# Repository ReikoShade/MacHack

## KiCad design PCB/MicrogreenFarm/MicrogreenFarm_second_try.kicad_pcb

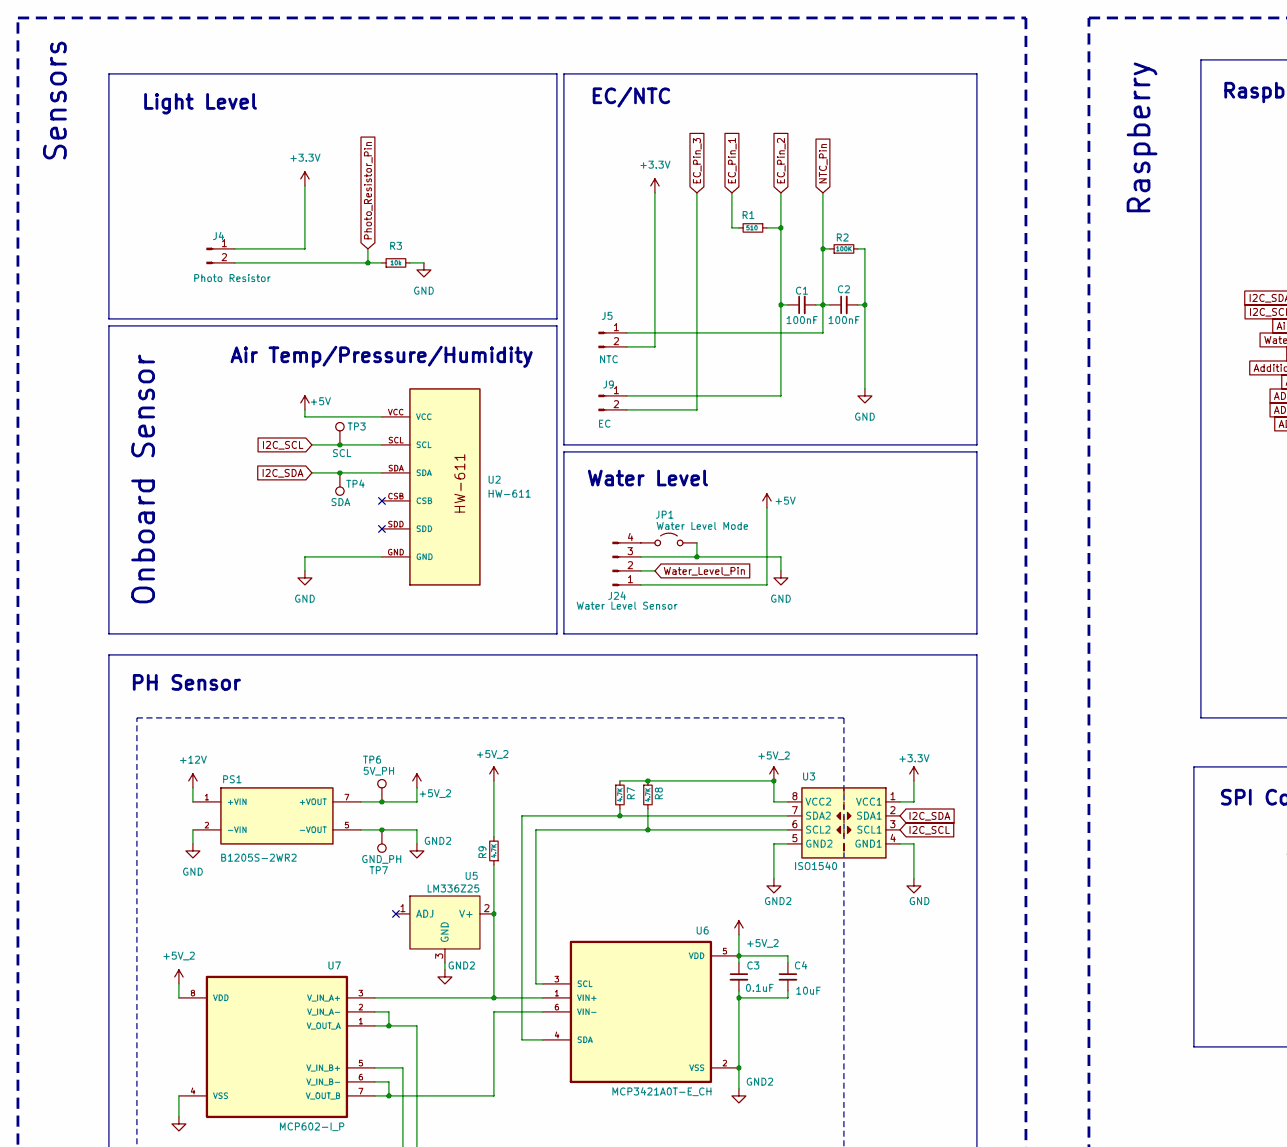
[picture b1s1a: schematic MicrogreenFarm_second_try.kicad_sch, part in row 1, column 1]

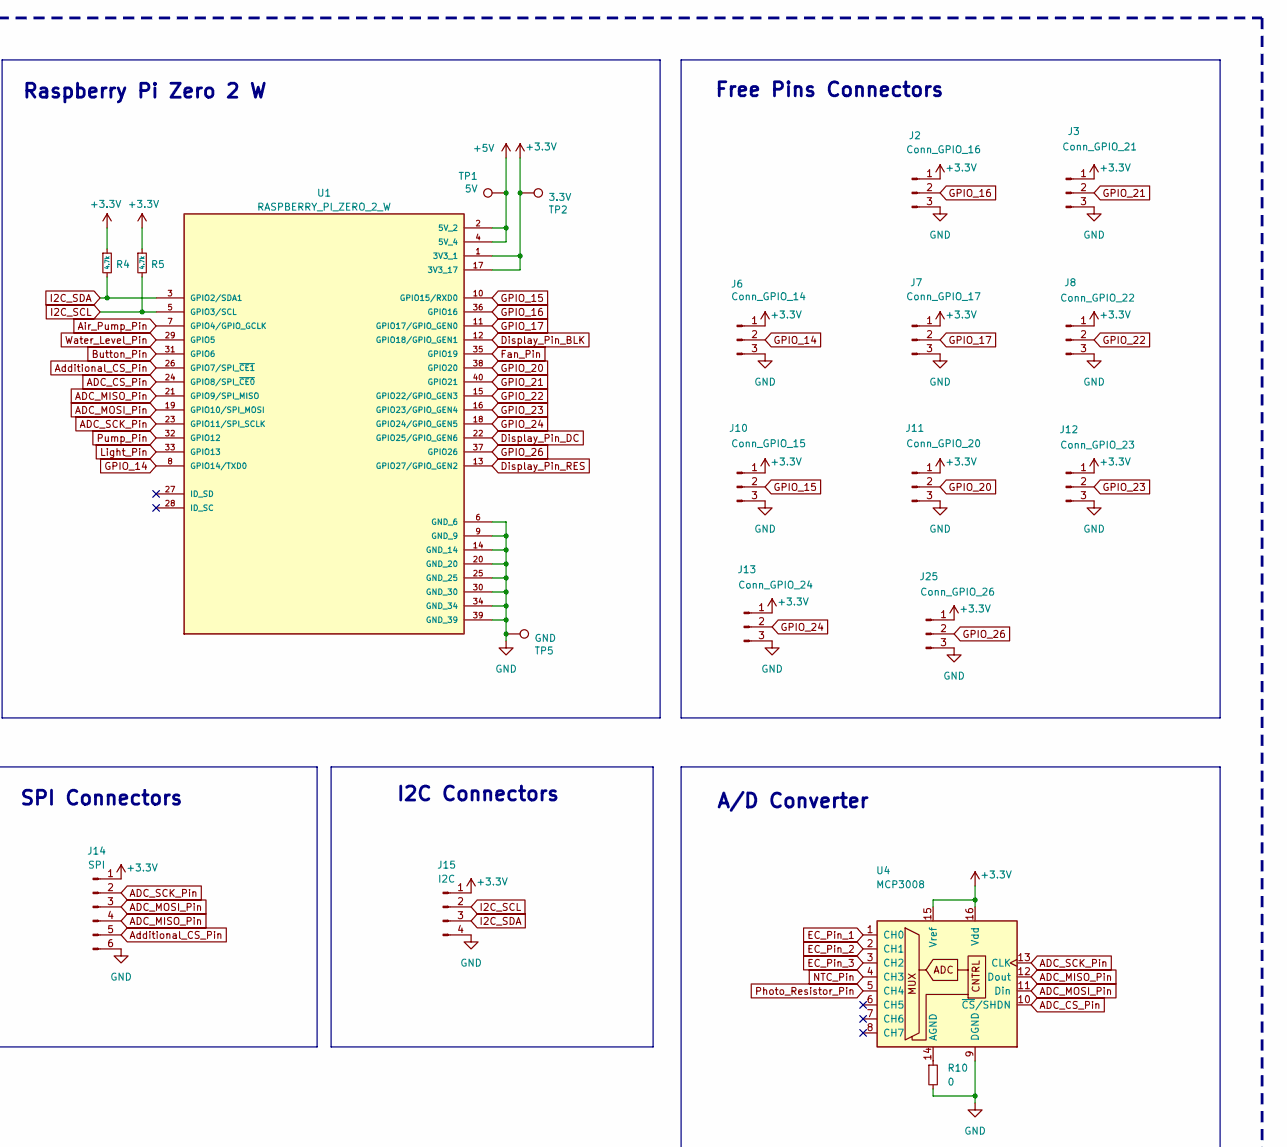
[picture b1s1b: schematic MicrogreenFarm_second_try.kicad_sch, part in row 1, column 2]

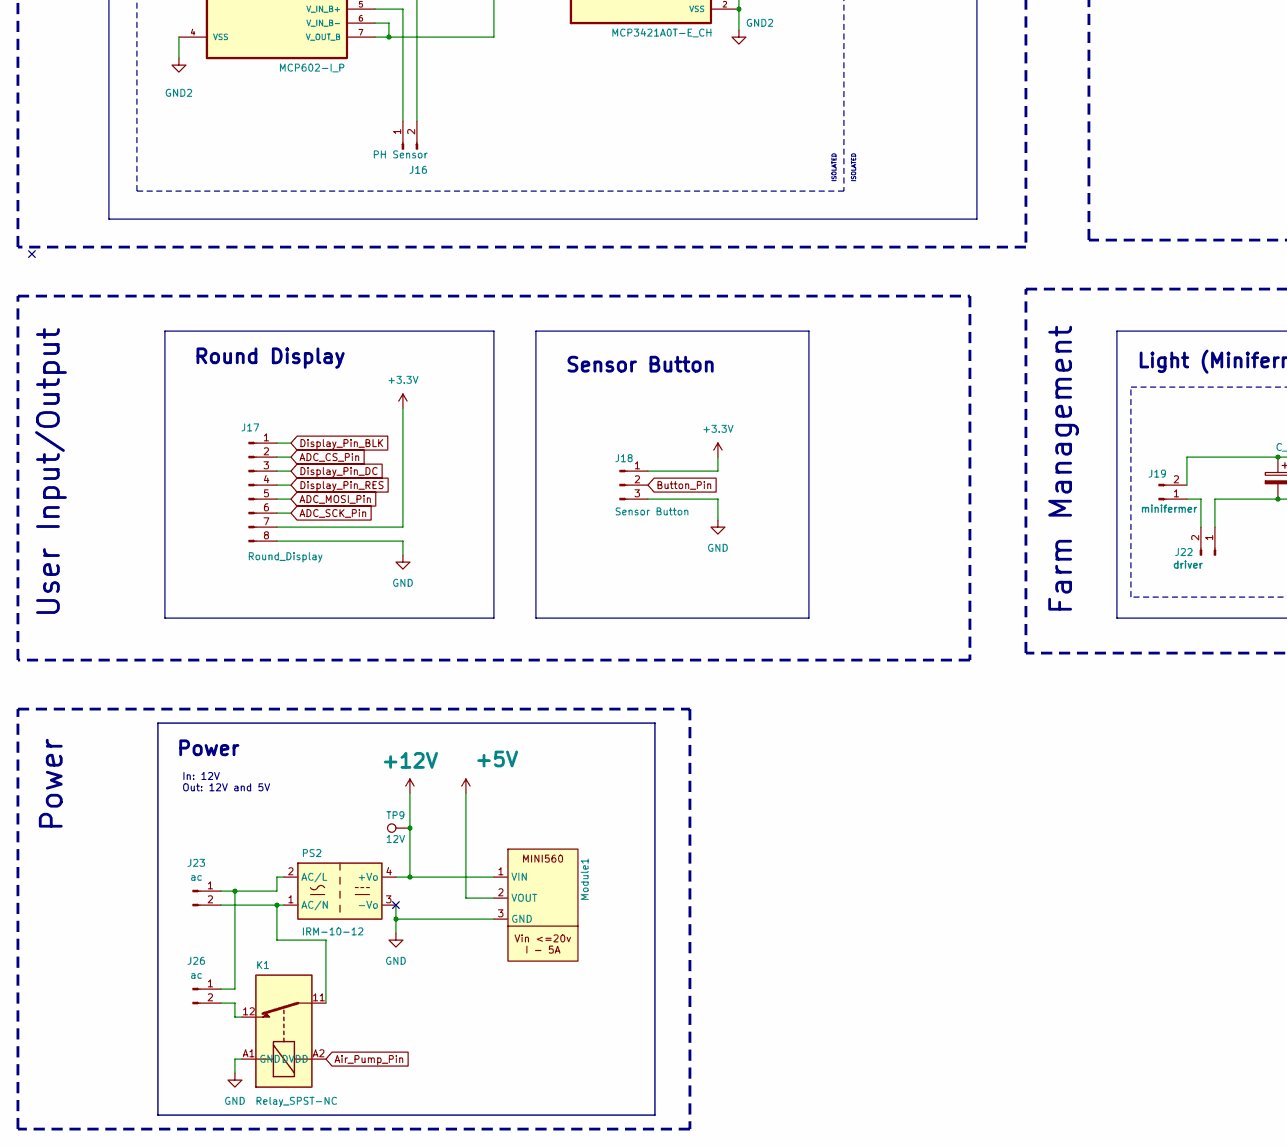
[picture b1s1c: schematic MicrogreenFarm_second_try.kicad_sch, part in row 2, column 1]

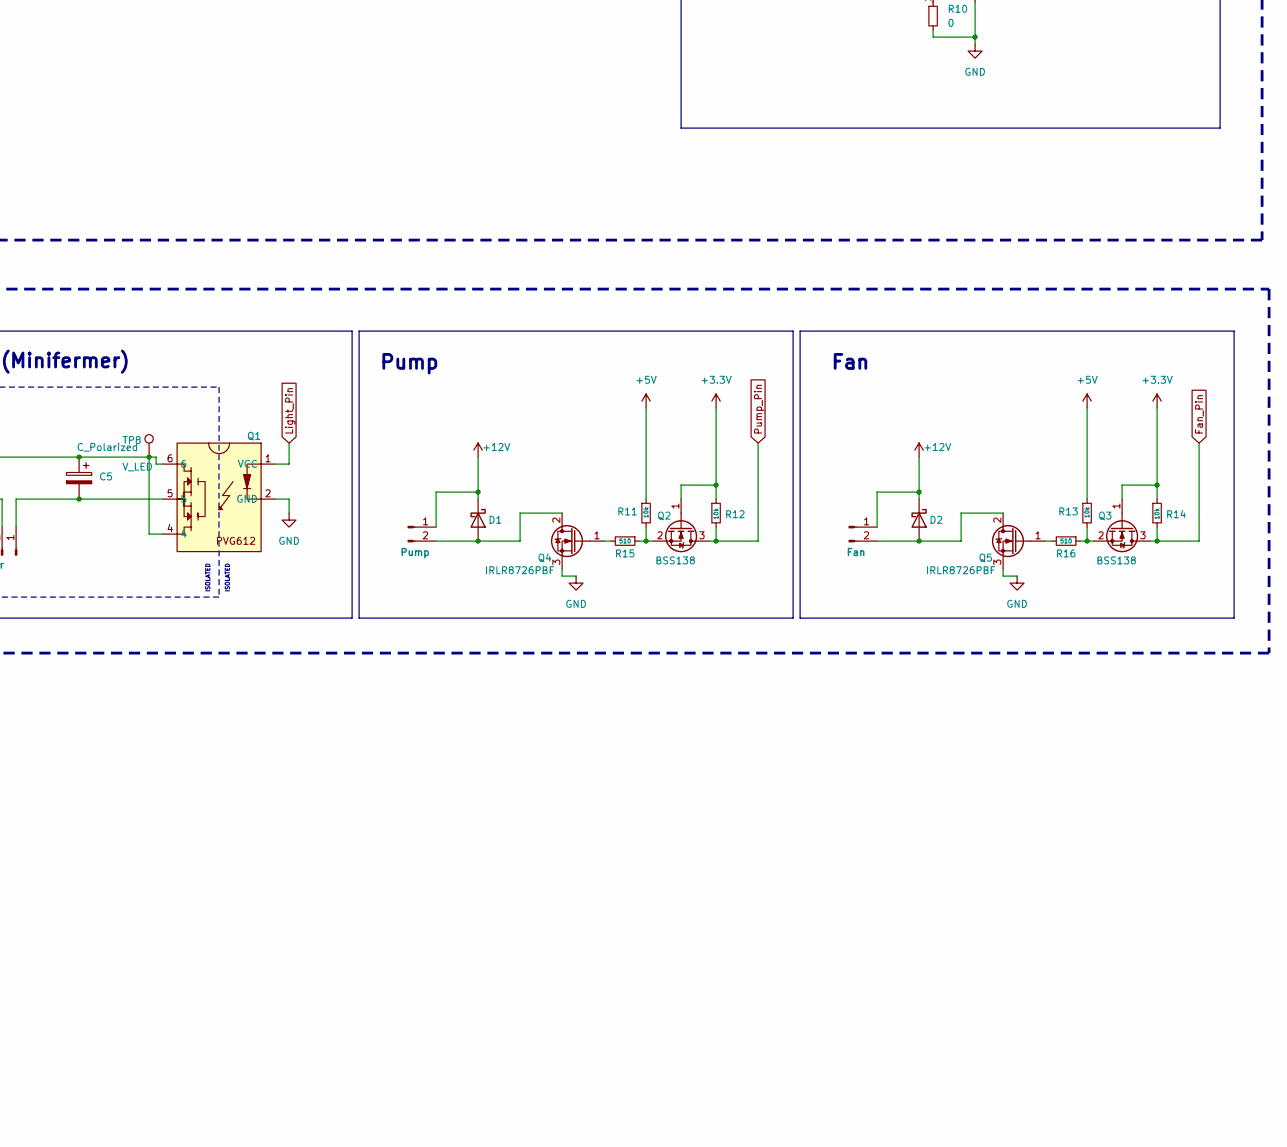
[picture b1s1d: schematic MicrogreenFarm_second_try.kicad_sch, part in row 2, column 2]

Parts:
C1, C2: 100nF; C_0402_1005Metric_Pad0.74x0.62mm_HandSolder
C3: 0.1uF; C_0402_1005Metric_Pad0.74x0.62mm_HandSolder
C4: 10uF; CP_EIA-3216-18_Kemet-A_Pad1.58x1.35mm_HandSolder
C5: C_Polarized; CP_Radial_D10.0mm_P3.80mm
D1, D2: SS34; D_SMA
J2: Conn_GPIO_16; PinHeader_1x03_P2.54mm_Vertical
J3: Conn_GPIO_21; PinHeader_1x03_P2.54mm_Vertical
J4: Photo Resistor; JST_XH_B2B-XH-A_1x02_P2.50mm_Vertical
J5: NTC; JST_XH_B2B-XH-A_1x02_P2.50mm_Vertical
J6: Conn_GPIO_14; PinHeader_1x03_P2.54mm_Vertical
J7: Conn_GPIO_17; PinHeader_1x03_P2.54mm_Vertical
J8: Conn_GPIO_22; PinHeader_1x03_P2.54mm_Vertical
J9: EC; JST_XH_B2B-XH-A_1x02_P2.50mm_Vertical
J10: Conn_GPIO_15; PinHeader_1x03_P2.54mm_Vertical
J11: Conn_GPIO_20; PinHeader_1x03_P2.54mm_Vertical
J12: Conn_GPIO_23; PinHeader_1x03_P2.54mm_Vertical
J13: Conn_GPIO_24; PinHeader_1x03_P2.54mm_Vertical
J14: SPI; JST_XH_B6B-XH-A_1x06_P2.50mm_Vertical
J15: I2C; JST_XH_B4B-XH-A_1x04_P2.50mm_Vertical
J16: PH Sensor; DOSIN-801-0051-thumbnail1DOSIN-801-0051
J17: Round_Display; JST_XH_B8B-XH-A_1x08_P2.50mm_Vertical
J18: Sensor Button; JST_XH_B3B-XH-A_1x03_P2.50mm_Vertical
J19: minifermer; WAGO_2060-452_998-404
J20: Pump; JST_XH_B2B-XH-A_1x02_P2.50mm_Vertical
J21: Fan; JST_XH_B2B-XH-A_1x02_P2.50mm_Vertical
J22: driver; WAGO_2060-452_998-404
J23, J26: ac; WAGO_2060-452_998-404
J24: Water Level Sensor; JST_XH_B4B-XH-A_1x04_P2.50mm_Vertical
J25: Conn_GPIO_26; PinHeader_1x03_P2.54mm_Vertical
JP1: Water Level Mode; SolderJumper-2_P1.3mm_Open_RoundedPad1.0x1.5mm
K1: Relay_SPST-NC; GOLD DDR SAI4005D_I
Module1: Mini560
PS1: B1205S-2WR2; PARTREV 2023-1.2
PS2: IRM-10-12; Converter_ACDC_MeanWell_IRM-10-xx_THT
Q1: DIP-6_W7.62mm
Q2, Q3: BSS138; SOT-23
Q4, Q5: IRLR8726PBF; TO-252-2
R1, R15, R16: 510; R_0402_1005Metric_Pad0.72x0.64mm_HandSolder
R2: 100K; R_0402_1005Metric_Pad0.72x0.64mm_HandSolder
R3, R11, R12, R13, R14: 10k; R_0402_1005Metric_Pad0.72x0.64mm_HandSolder
R4, R5: 4.7k; R_0402_1005Metric_Pad0.72x0.64mm_HandSolder
R7, R8, R9: 4.7K; R_0402_1005Metric_Pad0.72x0.64mm_HandSolder
R10: 0; SolderJumper-2_P1.3mm_Bridged_RoundedPad1.0x1.5mm
TP1: 5V; TestPoint_Pad_D2.0mm
TP2: 3.3V; TestPoint_Pad_D2.0mm
TP3: SCL; TestPoint_Pad_D2.0mm
TP4: SDA; TestPoint_Pad_D2.0mm
TP5: GND; TestPoint_Pad_D2.0mm
TP6: 5V_PH; TestPoint_Pad_D2.0mm
TP7: GND_PH; TestPoint_Pad_D2.0mm
TP8: V_LED; TestPoint_Pad_D2.0mm
TP9: 12V; TestPoint_Pad_D2.0mm
U1: RASPBERRY_PI_ZERO_2_W; MODULE_RASPBERRY_PI_ZERO_2_W; PARTREV April 2024
U2: HW-611
U3: ISO1540; SOIC-8_3.9x4.9mm_P1.27mm
U4: MCP3008; SOIC-16_3.9x9.9mm_P1.27mm
U5: LM336Z25
U6: MCP3421A0T-E_CH; SOT-23-6_Handsoldering
U7: MCP602-I_P; SOIC-8_3.9x4.9mm_P1.27mm

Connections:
+3.3V: J2.1, J3.1, J4.1, J5.2, J6.1, J7.1, J8.1, J10.1, J11.1, J12.1, J13.1, J14.1, J15.1, J17.7, J18.1, J25.1, Q2.1 (G), Q3.1 (G), R4.1, R5.1, R12.1, R14.1, TP2.1, U1.1 (3V3_1), U1.17 (3V3_17), U3.1 (VCC1), U4.15 (Vref), U4.16 (Vdd)
+5V: J24.1, Module1.2 (VOUT), R11.1, R13.1, TP1.1, U1.2 (5V_2), U1.4 (5V_4), U2.VCC
+5V_2: C3.1, C4.1, PS1.7 (+VOUT), R7.1, R8.1, R9.2, TP6.1, U3.8 (VCC2), U6.5 (VDD), U7.8 (VDD)
+12V: D1.1 (K), D2.1 (K), J20.1, J21.1, Module1.1 (VIN), PS1.1 (+VIN), PS2.4 (+Vo), TP9.1
ADC_CS_Pin: J17.2, U1.24 (GPIO8/SPI_~CE0), U4.10 (~CS/SHDN)
ADC_MISO_Pin: J14.4, U1.21 (GPIO9/SPI_MISO), U4.12 (Dout)
ADC_MOSI_Pin: J14.3, J17.5, U1.19 (GPIO10/SPI_MOSI), U4.11 (Din)
ADC_SCK_Pin: J14.2, J17.6, U1.23 (GPIO11/SPI_SCLK), U4.13 (CLK)
Additional_CS_Pin: J14.5, U1.26 (GPIO7/SPI_~CE1)
Air_Pump_Pin: K1.A2 (DVDD), U1.7 (GPIO4/GPIO_GCLK)
Button_Pin: J18.2, U1.31 (GPIO6)
Display_Pin_BLK: J17.1, U1.12 (GPIO18/GPIO_GEN1)
Display_Pin_DC: J17.3, U1.22 (GPIO25/GPIO_GEN6)
Display_Pin_RES: J17.4, U1.13 (GPIO27/GPIO_GEN2)
EC_Pin_1: R1.2, U4.1 (CH0)
EC_Pin_2: C1.1, J9.1, R1.1, U4.2 (CH1)
EC_Pin_3: J9.2, U4.3 (CH2)
Fan_Pin: Q3.3 (D), R14.2, U1.35 (GPIO19)
GND: C2.2, J2.3, J3.3, J6.3, J7.3, J8.3, J10.3, J11.3, J12.3, J13.3, J14.6, J15.4, J17.8, J18.3, J24.3, J25.3, JP1.2 (B), K1.A1 (GND), Module1.3 (GND), PS1.2 (-VIN), PS2.3 (-Vo), Q1.2 (GND), Q4.3 (S), Q5.3 (S), R2.2, R3.2, R10.2, TP5.1, U1.6 (GND_6), U1.9 (GND_9), U1.14 (GND_14), U1.20 (GND_20), U1.25 (GND_25), U1.30 (GND_30), U1.34 (GND_34), U1.39 (GND_39), U2.GND, U3.4 (GND1), U4.9 (DGND)
GND2: C3.2, C4.2, PS1.5 (-VOUT), TP7.1, U3.5 (GND2), U5.3 (GND), U6.2 (VSS), U7.4 (VSS)
GPIO_14: J6.2, U1.8 (GPIO14/TXD0)
GPIO_15: J10.2, U1.10 (GPIO15/RXD0)
GPIO_16: J2.2, U1.36 (GPIO16)
GPIO_17: J7.2, U1.11 (GPIO17/GPIO_GEN0)
GPIO_20: J11.2, U1.38 (GPIO20)
GPIO_21: J3.2, U1.40 (GPIO21)
GPIO_22: J8.2, U1.15 (GPIO22/GPIO_GEN3)
GPIO_23: J12.2, U1.16 (GPIO23/GPIO_GEN4)
GPIO_24: J13.2, U1.18 (GPIO24/GPIO_GEN5)
GPIO_26: J25.2, U1.37 (GPIO26)
I2C_SCL: J15.2, R5.2, TP3.1, U1.5 (GPIO3/SCL), U2.SCL, U3.3 (SCL1)
I2C_SDA: J15.3, R4.2, TP4.1, U1.3 (GPIO2/SDA1), U2.SDA, U3.2 (SDA1)
Light_Pin: Q1.1 (VCC), U1.33 (GPIO13)
NTC_Pin: C1.2, C2.1, J5.1, R2.1, U4.4 (CH3)
unnamed: D1.2 (A), J20.2, Q4.2 (D)
unnamed: D2.2 (A), J21.2, Q5.2 (D)
unnamed: J16.1, U7.5 (V_IN_B+)
unnamed: J16.2, U7.1 (V_OUT_A), U7.2 (V_IN_A-)
unnamed: J19.1, J22.2
unnamed: C5.1, J19.2, Q1.4, Q1.6, TP8.1
unnamed: C5.2, J22.1, Q1.5
unnamed: J23.1, J26.1, PS2.2 (AC/L)
unnamed: J23.2, K1.11, PS2.1 (AC/N)
unnamed: J24.4, JP1.1 (A)
unnamed: J26.2, K1.12
unnamed: Q2.2 (S), R11.2, R15.1
unnamed: Q3.2 (S), R13.2, R16.1
unnamed: Q4.1 (G), R15.2
unnamed: Q5.1 (G), R16.2
unnamed: R8.2, U3.6 (SCL2), U6.3 (SCL)
unnamed: R7.2, U3.7 (SDA2), U6.4 (SDA)
unnamed: R10.1, U4.14 (AGND)
unnamed: R9.1, U5.2 (V+), U6.1 (VIN+), U7.3 (V_IN_A+)
unnamed: U6.6 (VIN-), U7.6 (V_IN_B-), U7.7 (V_OUT_B)
Photo_Resistor_Pin: J4.2, R3.1, U4.5 (CH4)
Pump_Pin: Q2.3 (D), R12.2, U1.32 (GPIO12)
Water_Level_Pin: J24.2, U1.29 (GPIO5)

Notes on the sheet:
ISOLATED
Farm Management
EC/NTC
Fan
User Input/Output
Power
Round Display
Sensors
In: 12V Out: 12V and 5V
Water Level
Air Temp/Pressure/Humidity
Raspberry
Onboard Sensor
Light (Minifermer)
I2C Connectors
Light Level
A/D Converter
Sensor Button
Free Pins Connectors
SPI Connectors
Pump
PH Sensor
Raspberry Pi Zero 2 W

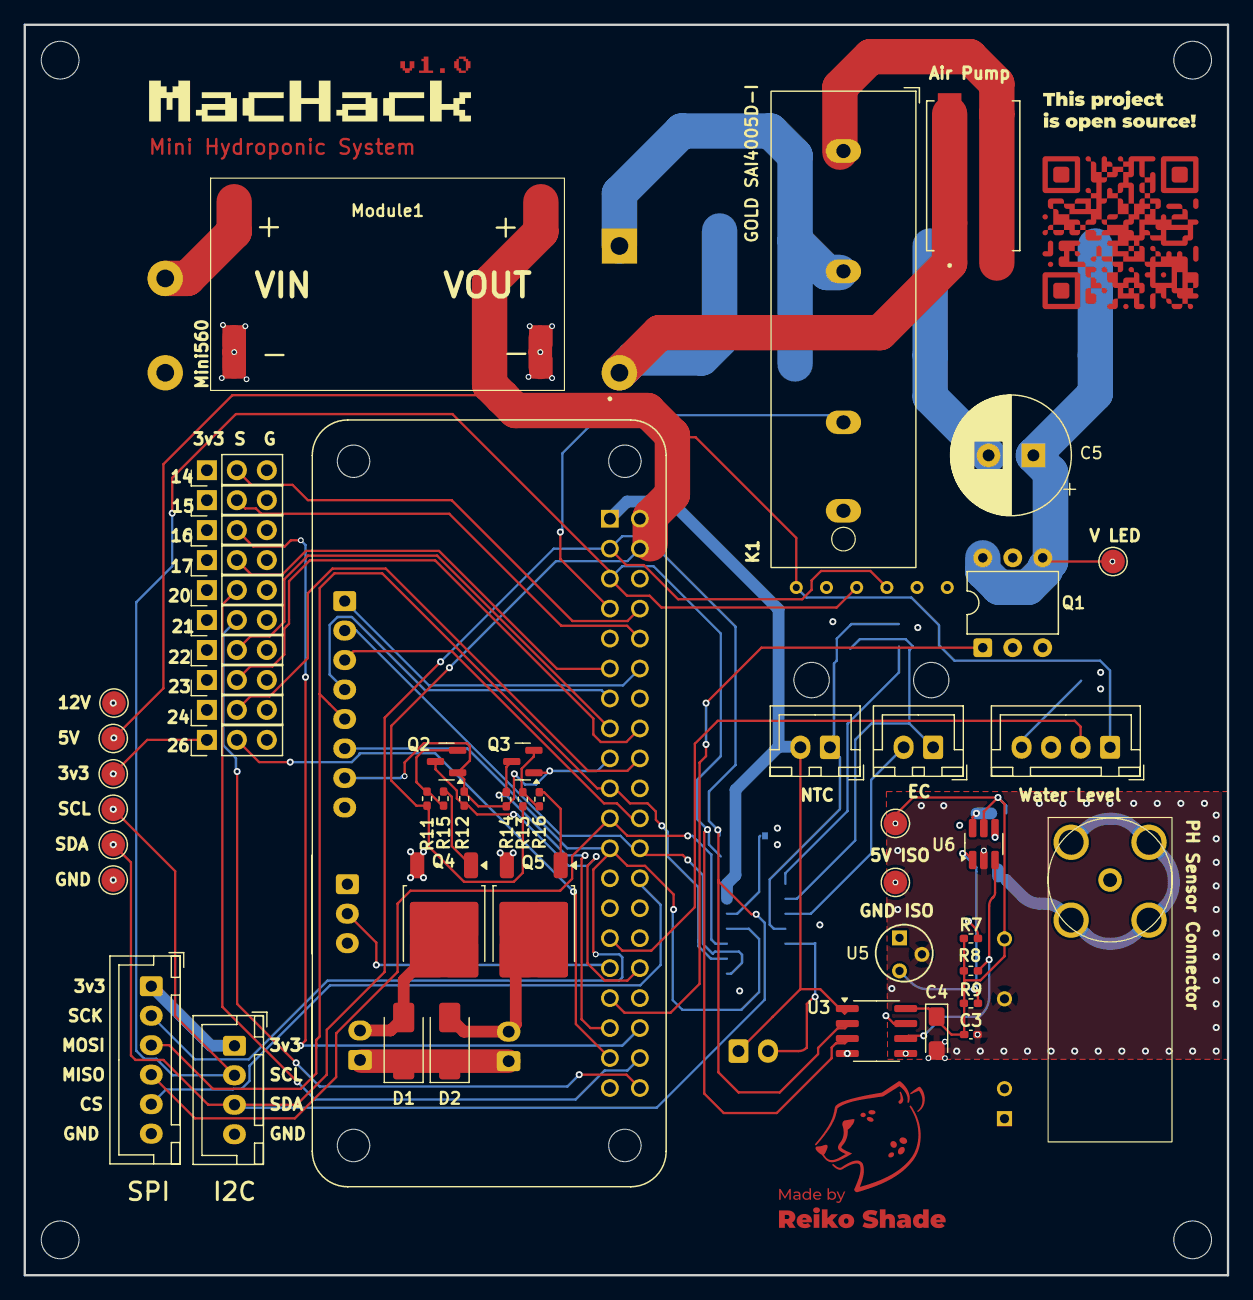
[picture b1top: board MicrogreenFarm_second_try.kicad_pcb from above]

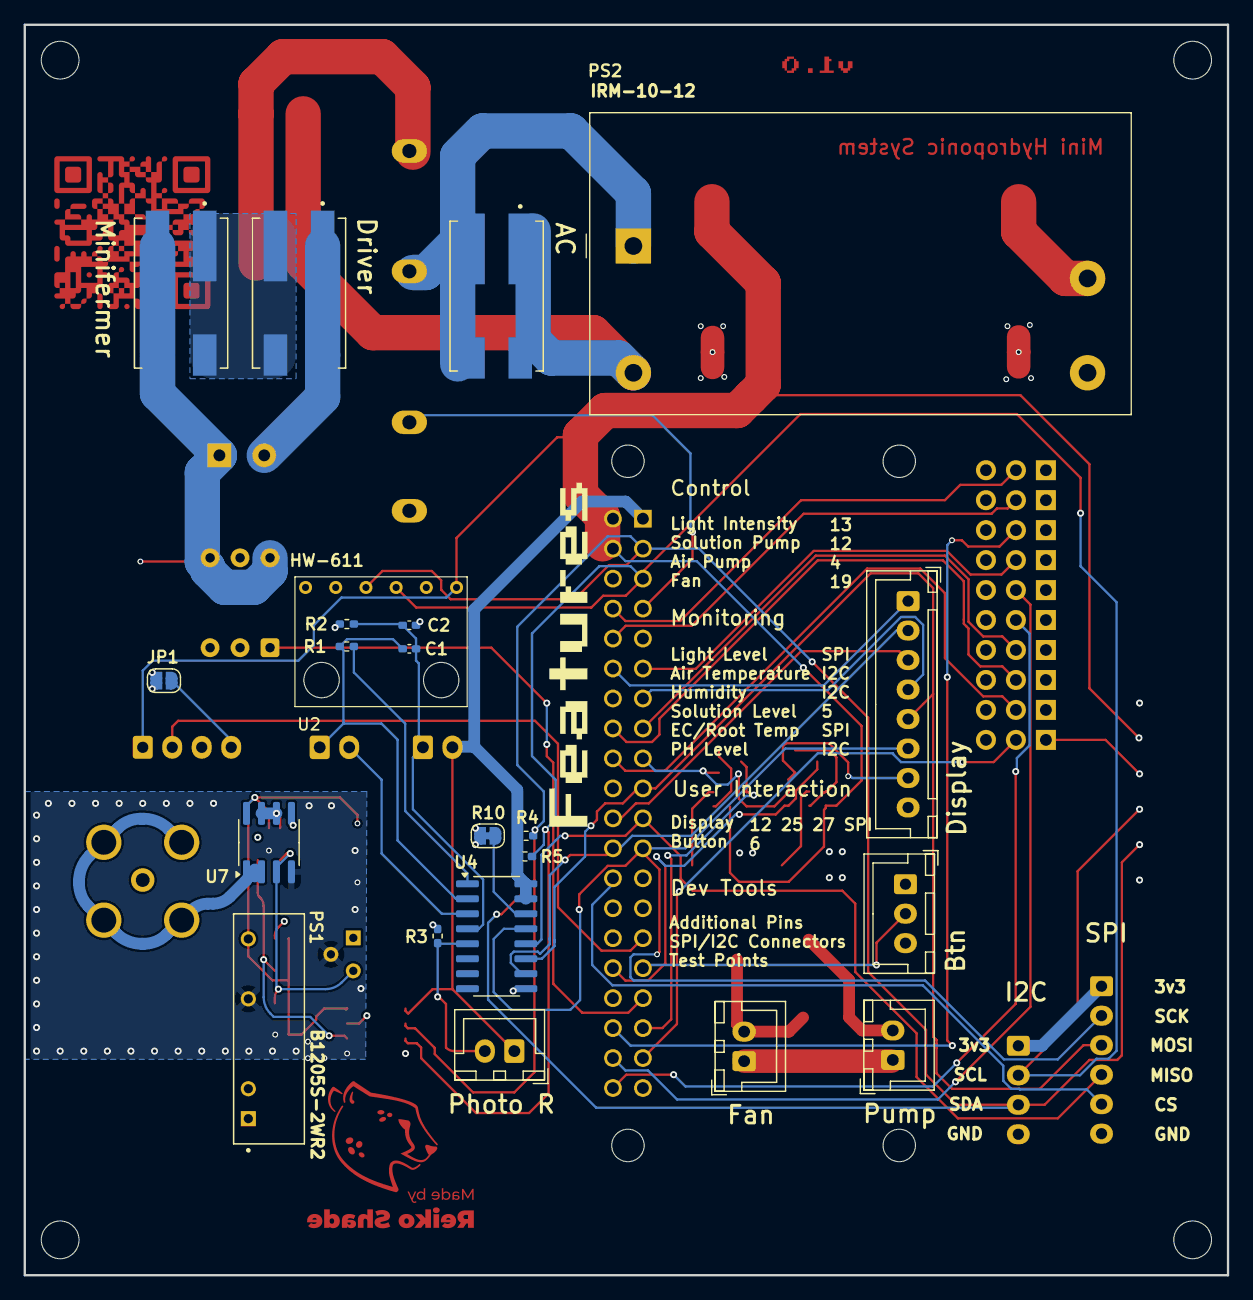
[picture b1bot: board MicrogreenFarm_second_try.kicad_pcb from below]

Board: 4 copper layers, 102.0 x 106.0 mm, 73 parts (22 on the bottom side), 57 nets.

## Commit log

2026-03-28 init
2026-03-28 Version 0.1
